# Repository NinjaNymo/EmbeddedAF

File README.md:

# EmbeddedAF
This repository contains the source code and hardware design files for a indoor automated urban farming system. 

The system has a master/slave architecture, where the master is refered to as the _master_, while the slaves as the _nodes_.

### **_The Concept:_**
The idea was to use a wireless sensor network system as a case study in an embedded systems development process.

Due to the master/slave architecture of the system, the project covers both embedded C development on the node devices and embedded Linux development on the master device, as well as communication over ZigBee between the two.

All in all; a good variation of challanges to learn more about embedded systems.

### **_The Node:_**

The node features a 16-bit MCU and a XBee 3 ZigBee module on an in-house developed and etched PCB. An OLED display and buttons are included on the board such that the node device can be used in an _offline mode_ independetly of the master device.

The node device measures temperature on the PCB and interfaces with 1) external digital temperature sensors, 2) an external analog soil moisture sensor and 3) an external relay that controls a grow-light.

The idea is to control the grow-light on a day/night-like cycle and record and publish the temperature and soil moisture measurements to the master device.

* The firmware is written in C, and can be found in [/src/node/](/src/node).
* The schematic and PCB is designed in Eagle, and can be found in [/Eagle/node/](/Eagle/node/).

This repository contains stuff for a project on embedded automatic farming.

That includes circuit schematics, PCB designs and code to run on the two systems:

1. **The node:** A board with a 16-bit MCU and a XBee 3 micro module. It features two temperature sensors and one analog soil moisture sensor as well as I/O for offline availiability. The source found in src/node is written C and compiles with XC16.
2. **The master:** A Raspberry Pi 2B mounted with the same XB3 modules as the nodes. It runs Raspbian Stretch lite, a MQTT broker, a Node.js server that provides a web ui and finally a MQTT-SN gateway that is implemented in python and who's source code is found in src/master.

In addition there are some random python scripts, diagrams in the DrawIO folder, prototype schematics and board designs.

### The concept:

The idea here is to use a wireless sensor network system inteded to be used in indoor automatic farming as a case study in a development process.

I like watching things grow, and I think indoor has interesting benefits over traditional outdoor farming such as reduced water consumption, seasonal independence and a shorter logistic travel distance so perhaps some day all this might turn into something.

To do automated farming, it controls a LED lamp on a day/night-like cycle which can be configured through the on-board user interface or wirelessly.

The lamp and power distribution needs some work and will be put up here once it is up to spec. 

Further the node measures water content in soil which is intended to be used with automated watering. It has a Dallas 1-wire bus on one of it connectors which currently run both an on-board temp sensor and an external waterproof one that I planned on sticking in the soil.

The MCU does everything mentioned above, and UARTs with the XB3 which handle MQTT over ZigBee.

With many of these and an online master device from which you can monitor and control the whole setup it should be possible to realize indoor automated farming.

### Technical details:

#### The node:
* Microchip PIC24FJ128GA202 MCU. 16-bit.
* Digi XB3-24Z8UM RF module running ZigBee 3.0 API as a router.
* Maxim DS18B20 temperature sensors.
* Analog capacative soil moisture sensor.
* SSD1306 OLED display driver.
*

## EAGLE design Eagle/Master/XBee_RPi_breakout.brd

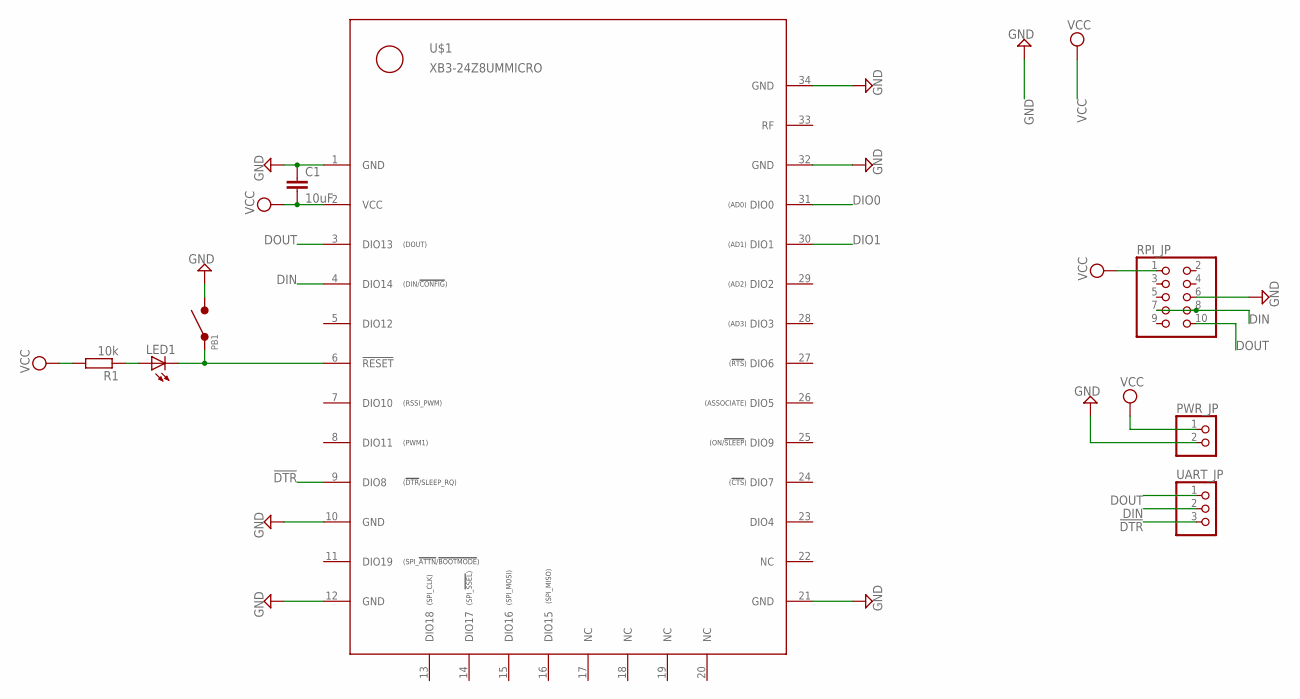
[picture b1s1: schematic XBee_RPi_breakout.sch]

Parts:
C1: 10uF; C0805
LED1: LEDSML0805; SML0805
PB1: PUSHBUTTON_2LEG; PUSHBUTTON_6X3.5MM
PWR_JP: PINHD-1X2; 1X02
R1: 10k; M0805
RPI_JP: PINHD-2X5; 2X05
U$1: XB3-24Z8UMMICRO; XBEE3_MICRO
UART_JP: PINHD-1X3; 1X03

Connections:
!DTR: U$1.9 (DIO8), UART_JP.3
!RST: LED1.C, PB1.P$1, U$1.6 (!RESET)
DIN: RPI_JP.7, RPI_JP.8, U$1.4 (DIO14), UART_JP.2
DIO0: U$1.31 (DIO0)
DIO1: U$1.30 (DIO1)
DOUT: RPI_JP.10, U$1.3 (DIO13), UART_JP.1
GND: C1.1, PB1.P$2, PWR_JP.2, RPI_JP.6, U$1.1 (GND), U$1.10 (GND), U$1.12 (GND), U$1.21 (GND), U$1.32 (GND), U$1.34 (GND)
unnamed: LED1.A, R1.1
VCC: C1.2, PWR_JP.1, R1.2, RPI_JP.1, U$1.2 (VCC)

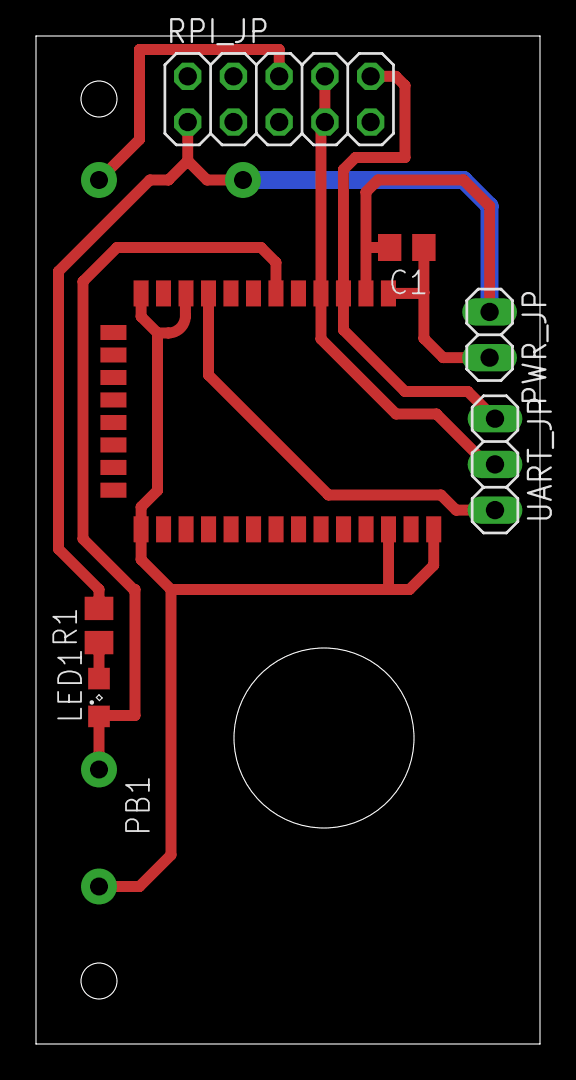
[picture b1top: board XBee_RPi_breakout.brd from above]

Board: 2 copper layers, 28.0 x 56.0 mm, 8 parts (0 on the bottom side), 7 nets.

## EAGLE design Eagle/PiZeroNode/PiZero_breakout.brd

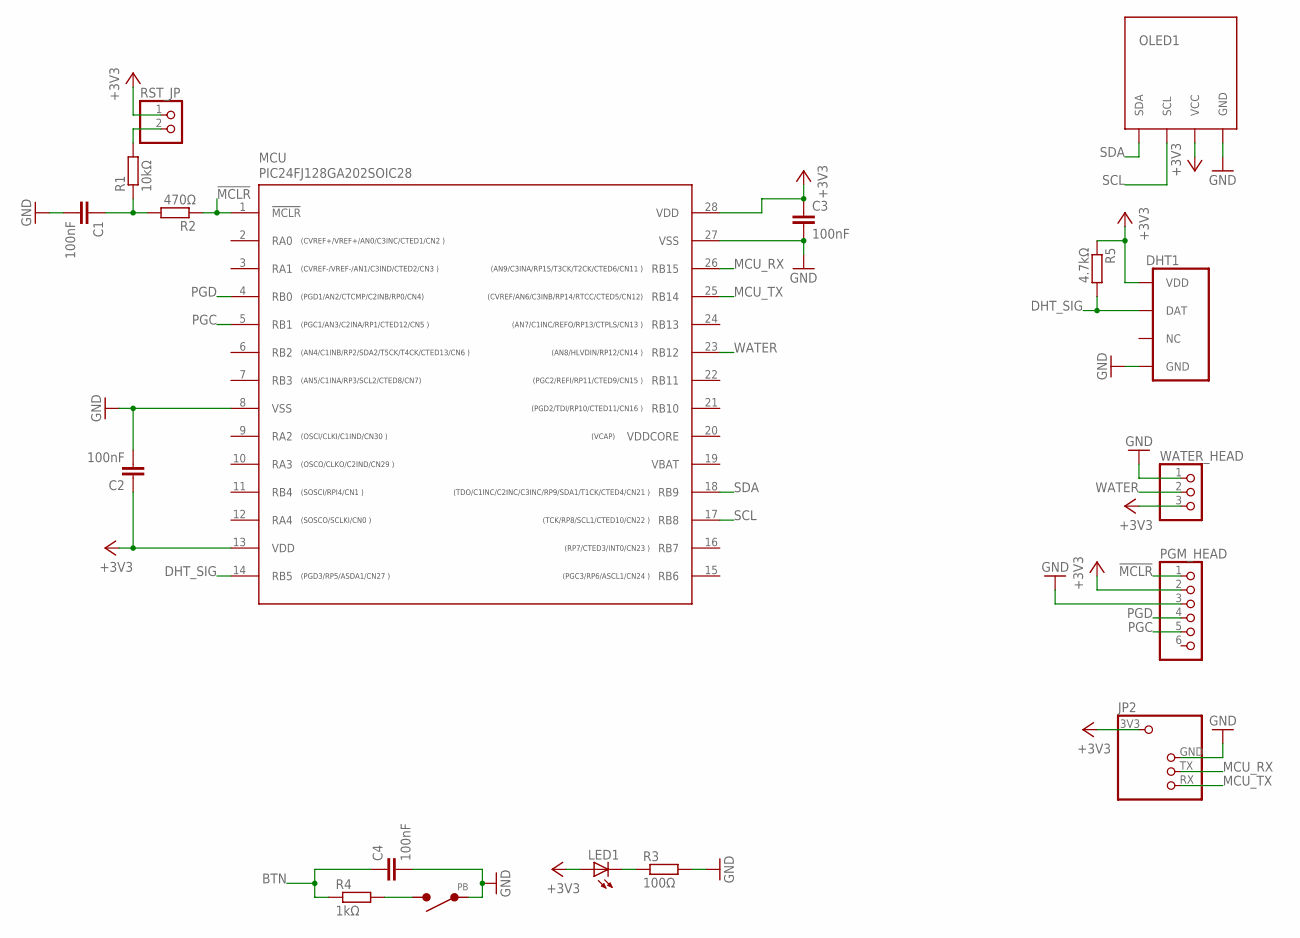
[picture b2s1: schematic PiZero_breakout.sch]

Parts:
C1, C2, C3, C4: 100nF; C0805
DHT1: DHT11VERT; DHT11
JP2: RPI_UART_HEADER; RPI_UART_HEAD
LED1: LEDCHIPLED_0805; CHIPLED_0805
MCU: PIC24FJ128GA202SOIC28; SOIC28L
OLED1: OLED_4PIN_I2C; OLED_4PIN
PB: PUSHBUTTON_2LEG; PUSHBUTTON_6X3.5MM
PGM_HEAD: PINHD-1X6; 1X06
R1: 10kΩ; R0805
R2: 470Ω; R0805
R3: 100Ω; R0805
R4: 1kΩ; R0805
R5: 4.7kΩ; R0805
RST_JP: PINHD-1X2; 1X02
WATER_HEAD: PINHD-1X3; 1X03

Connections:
!MCLR: MCU.1 (!MCLR), PGM_HEAD.1, R2.1
+3V3: C2.1, C3.1, DHT1.VDD, JP2.3V3, LED1.A, MCU.13 (VDD), MCU.28 (VDD), OLED1.VCC, PGM_HEAD.2, R5.1, RST_JP.1, WATER_HEAD.3
BTN: C4.1, R4.1
DHT_SIG: DHT1.DAT, MCU.14 (RB5), R5.2
GND: C1.2, C2.2, C3.2, C4.2, DHT1.GND, JP2.GND, MCU.8 (VSS), MCU.27 (VSS), OLED1.GND, PB.P$1, PGM_HEAD.3, R3.2, WATER_HEAD.1
MCU_RX: JP2.TX, MCU.26 (RB15)
MCU_TX: JP2.RX, MCU.25 (RB14)
unnamed: C1.1, R1.1, R2.2
unnamed: LED1.C, R3.1
unnamed: R1.2, RST_JP.2
unnamed: PB.P$2, R4.2
PGC: MCU.5 (RB1), PGM_HEAD.5
PGD: MCU.4 (RB0), PGM_HEAD.4
SCL: MCU.17 (RB8), OLED1.SCL
SDA: MCU.18 (RB9), OLED1.SDA
VDDCORE: MCU.20 (VDDCORE)
WATER: MCU.23 (RB12), WATER_HEAD.2

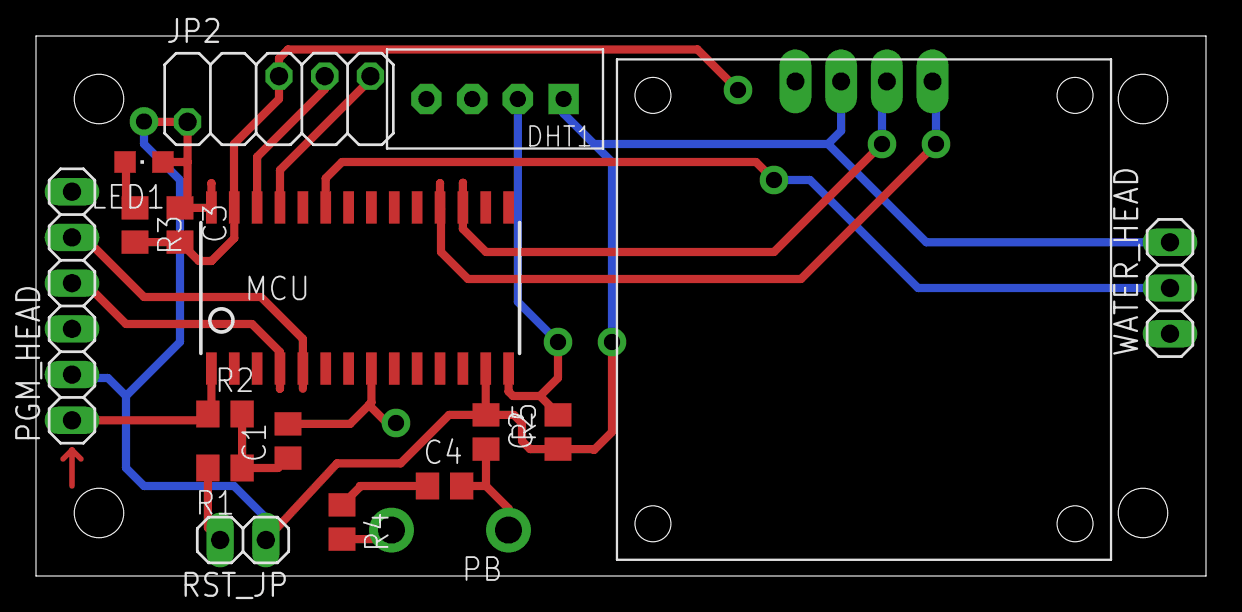
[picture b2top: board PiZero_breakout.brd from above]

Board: 2 copper layers, 65.0 x 30.0 mm, 18 parts (0 on the bottom side), 16 nets.

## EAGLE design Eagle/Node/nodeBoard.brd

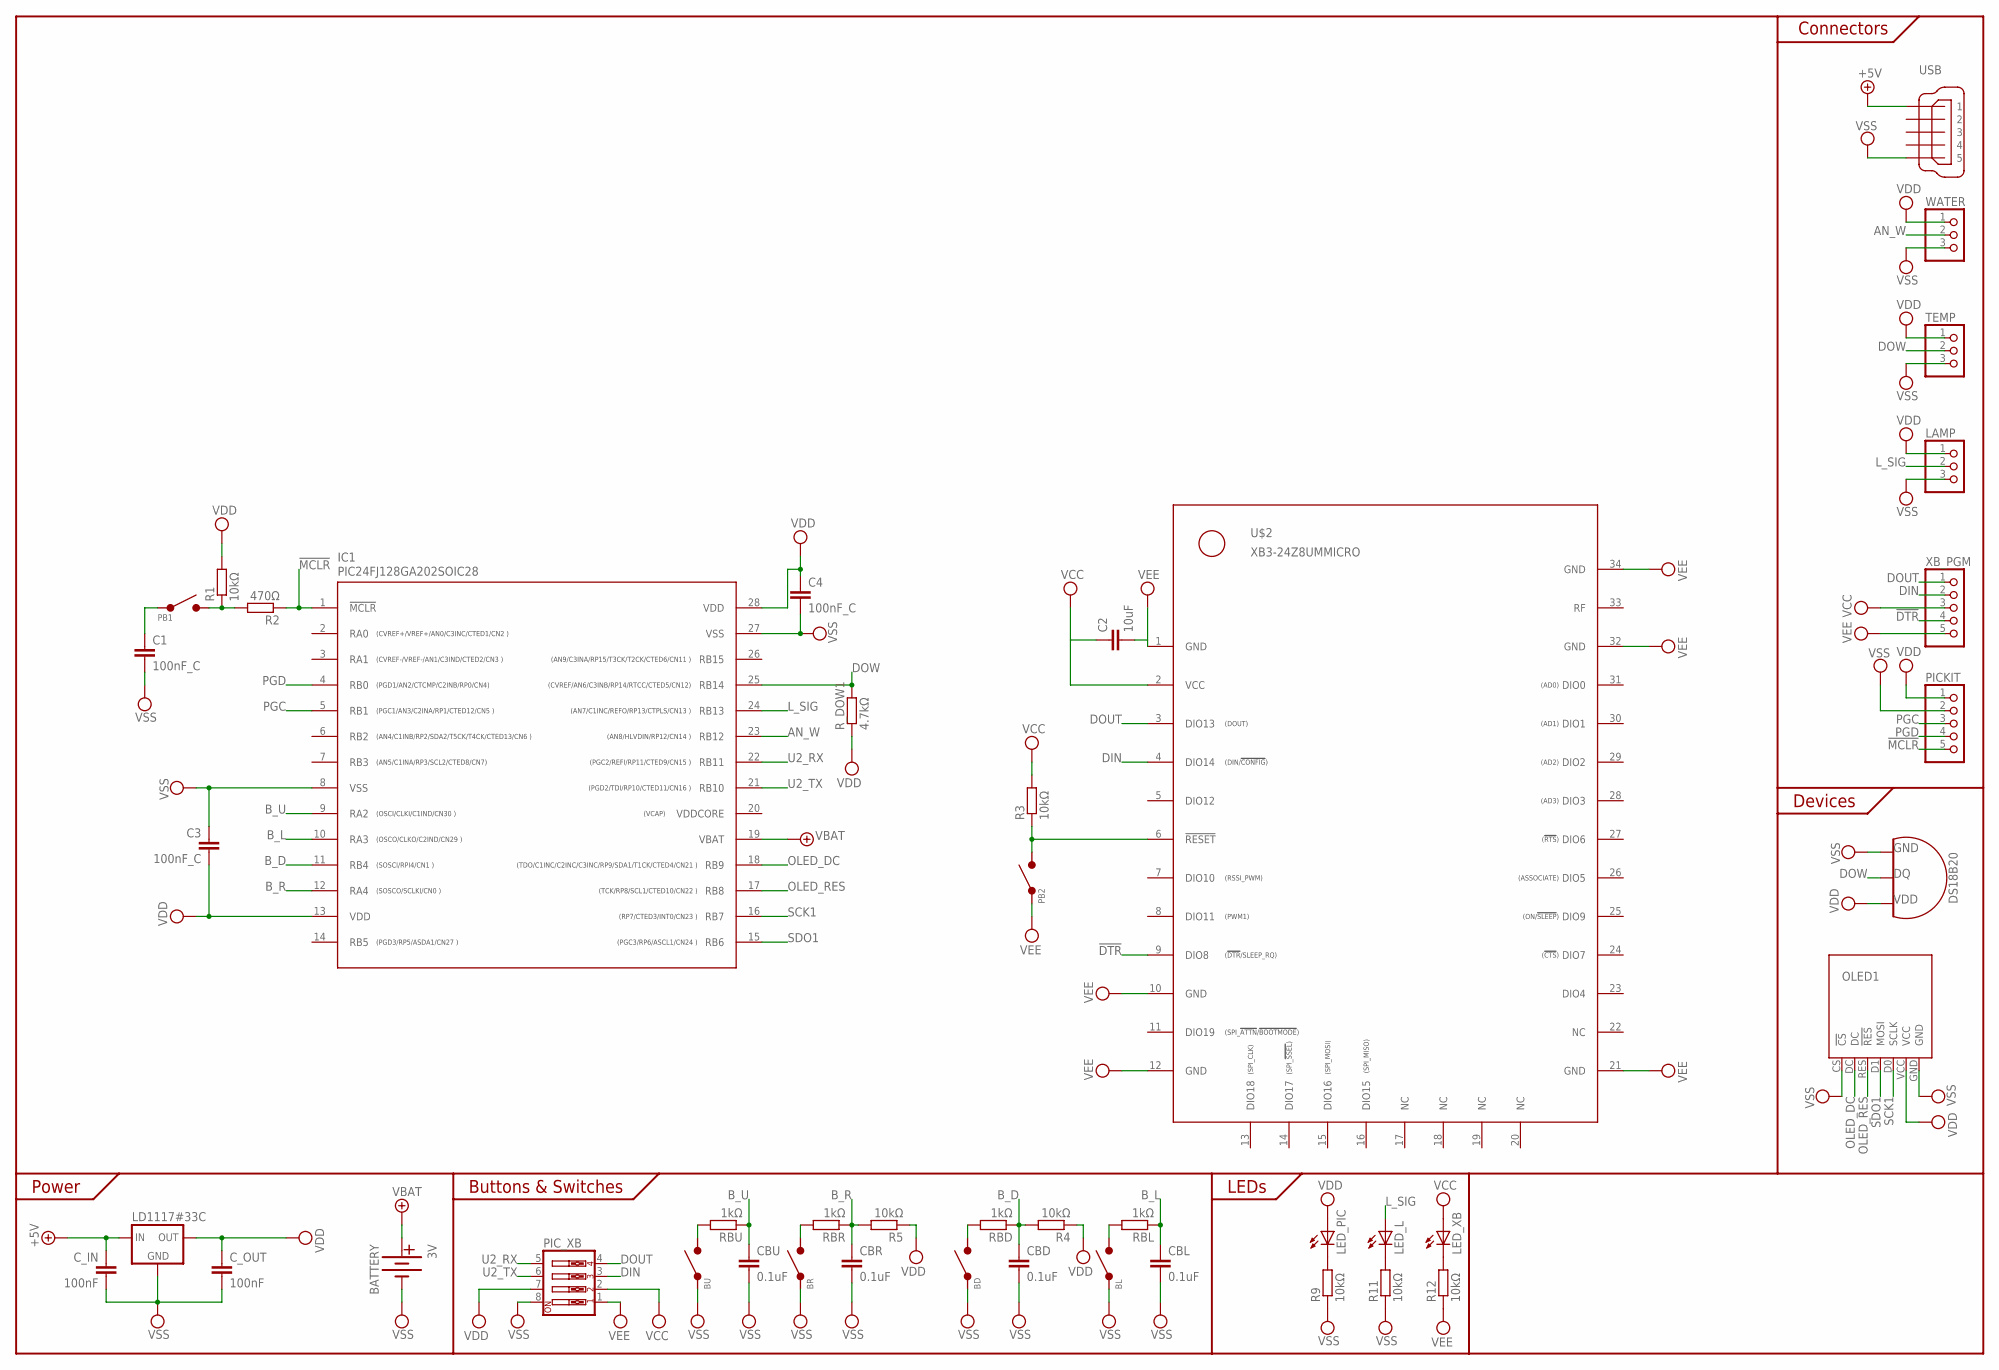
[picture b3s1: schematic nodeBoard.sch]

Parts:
3V: BATTERY; 20MM_CELLHOLDER
BD: PUSHBUTTON_4LEG_SMD; TACTILE_SWITCH_SMD_6.2MM_BROWN
BL: PUSHBUTTON_4LEG_SMD; TACTILE_SWITCH_SMD_6.2MM_BROWN
BR: PUSHBUTTON_4LEG_SMD; TACTILE_SWITCH_SMD_6.2MM_BROWN
BU: PUSHBUTTON_4LEG_SMD; TACTILE_SWITCH_SMD_6.2MM_BROWN
C1, C3, C4: 100nF_C; C0805
C2: 10uF; C0805
CBD: 0.1uF; C0805
CBL: 0.1uF; C0805
CBR: 0.1uF; C0805
CBU: 0.1uF; C0805
C_IN: 100nF; C0805
C_OUT: 100nF; C0805
IC1: PIC24FJ128GA202SOIC28; SOIC28L
LAMP: PINHD-1X3; 1X03
LED_L: LEDCHIPLED_0805; CHIPLED_0805
LED_PIC: LEDCHIPLED_0805; CHIPLED_0805
LED_XB: LEDCHIPLED_0805; CHIPLED_0805
OLED1: OLED_7PIN_SPI; OLED_7PIN
PB1, PB2: PUSHBUTTON_2LEG; PUSHBUTTON_6X3.5MM
PICKIT: PINHD-1X5; 1X05
PIC_XB: SW_DIP-4; EDG-04
R1, R3, R4, R5, R9, R11, R12: 10kΩ; R0805
R2: 470Ω; R0805
RBD: 1kΩ; R0805
RBL: 1kΩ; R0805
RBR: 1kΩ; R0805
RBU: 1kΩ; R0805
R_DOW1: 4.7kΩ; R0805
TEMP: PINHD-1X3; 1X03
U$1: LD1117#33C; DPACK
U$2: XB3-24Z8UMMICRO; XBEE3_MICRO
U$7: DS18B20; TO92
USB: MINI-USB-32005-201; 32005-201
WATER: PINHD-1X3; 1X03
XB_PGM: PINHD-1X5; 1X05

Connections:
!DTR: U$2.9 (DIO8), XB_PGM.4
!MCLR: IC1.1 (!MCLR), PICKIT.5, R2.1
+5V: C_IN.1, U$1.3 (IN), USB.1
AN_W: IC1.23 (RB12), WATER.2
B_D: CBD.1, IC1.11 (RB4), R4.2, RBD.1
B_L: CBL.1, IC1.10 (RA3), RBL.1
B_R: CBR.1, IC1.12 (RA4), R5.2, RBR.1
B_U: CBU.1, IC1.9 (RA2), RBU.1
DIN: PIC_XB.3, U$2.4 (DIO14), XB_PGM.2
DOUT: PIC_XB.4, U$2.3 (DIO13), XB_PGM.1
DOW: IC1.25 (RB14), R_DOW1.2, TEMP.2, U$7.2 (DQ)
L_SIG: IC1.24 (RB13), LAMP.2, LED_L.A
unnamed: C1.1, PB1.P$1
unnamed: PB2.P$2, R3.1, U$2.6 (!RESET)
unnamed: PB1.P$2, R1.1, R2.2
unnamed: BU.B1, BU.B2, RBU.2
unnamed: BL.B1, BL.B2, RBL.2
unnamed: BR.B1, BR.B2, RBR.2
unnamed: BD.B1, BD.B2, RBD.2
unnamed: LED_L.C, R11.2
unnamed: LED_XB.C, R12.2
unnamed: LED_PIC.C, R9.2
OLED_DC: IC1.18 (RB9), OLED1.DC
OLED_RES: IC1.17 (RB8), OLED1.RES (!RES)
PGC: IC1.5 (RB1), PICKIT.3
PGD: IC1.4 (RB0), PICKIT.4
SCK1: IC1.16 (RB7), OLED1.D0 (SCLK)
SDO1: IC1.15 (RB6), OLED1.D1 (MOSI)
U2_RX: IC1.22 (RB11), PIC_XB.5
U2_TX: IC1.21 (RB10), PIC_XB.6
VBAT: 3V.+@1 (+), 3V.+@2 (+), IC1.19 (VBAT)
VCC: C2.1, LED_XB.A, PIC_XB.2, R3.2, U$2.2 (VCC), XB_PGM.3
VDD: C3.2, C4.1, C_OUT.1, IC1.13 (VDD), IC1.28 (VDD), LAMP.1, LED_PIC.A, OLED1.VCC, PICKIT.1, PIC_XB.7, R1.2, R4.1, R5.1, R_DOW1.1, TEMP.1, U$1.2 (OUT), U$7.3 (VDD), WATER.1
VDDCORE: IC1.20 (VDDCORE)
VEE: C2.2, PB2.P$1, PIC_XB.1, R12.1, U$2.1 (GND), U$2.10 (GND), U$2.12 (GND), U$2.21 (GND), U$2.32 (GND), U$2.34 (GND), XB_PGM.5
VSS: 3V.-, BD.A1, BD.A2, BL.A1, BL.A2, BR.A1, BR.A2, BU.A1, BU.A2, C1.2, C3.1, C4.2, CBD.2, CBL.2, CBR.2, CBU.2, C_IN.2, C_OUT.2, IC1.8 (VSS), IC1.27 (VSS), LAMP.3, OLED1.CS (!CS), OLED1.GND, PICKIT.2, PIC_XB.8, R9.1, R11.1, TEMP.3, U$1.1 (GND), U$7.1 (GND), USB.5, WATER.3

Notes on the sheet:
Power
Connectors
Buttons & Switches
Devices
LEDs

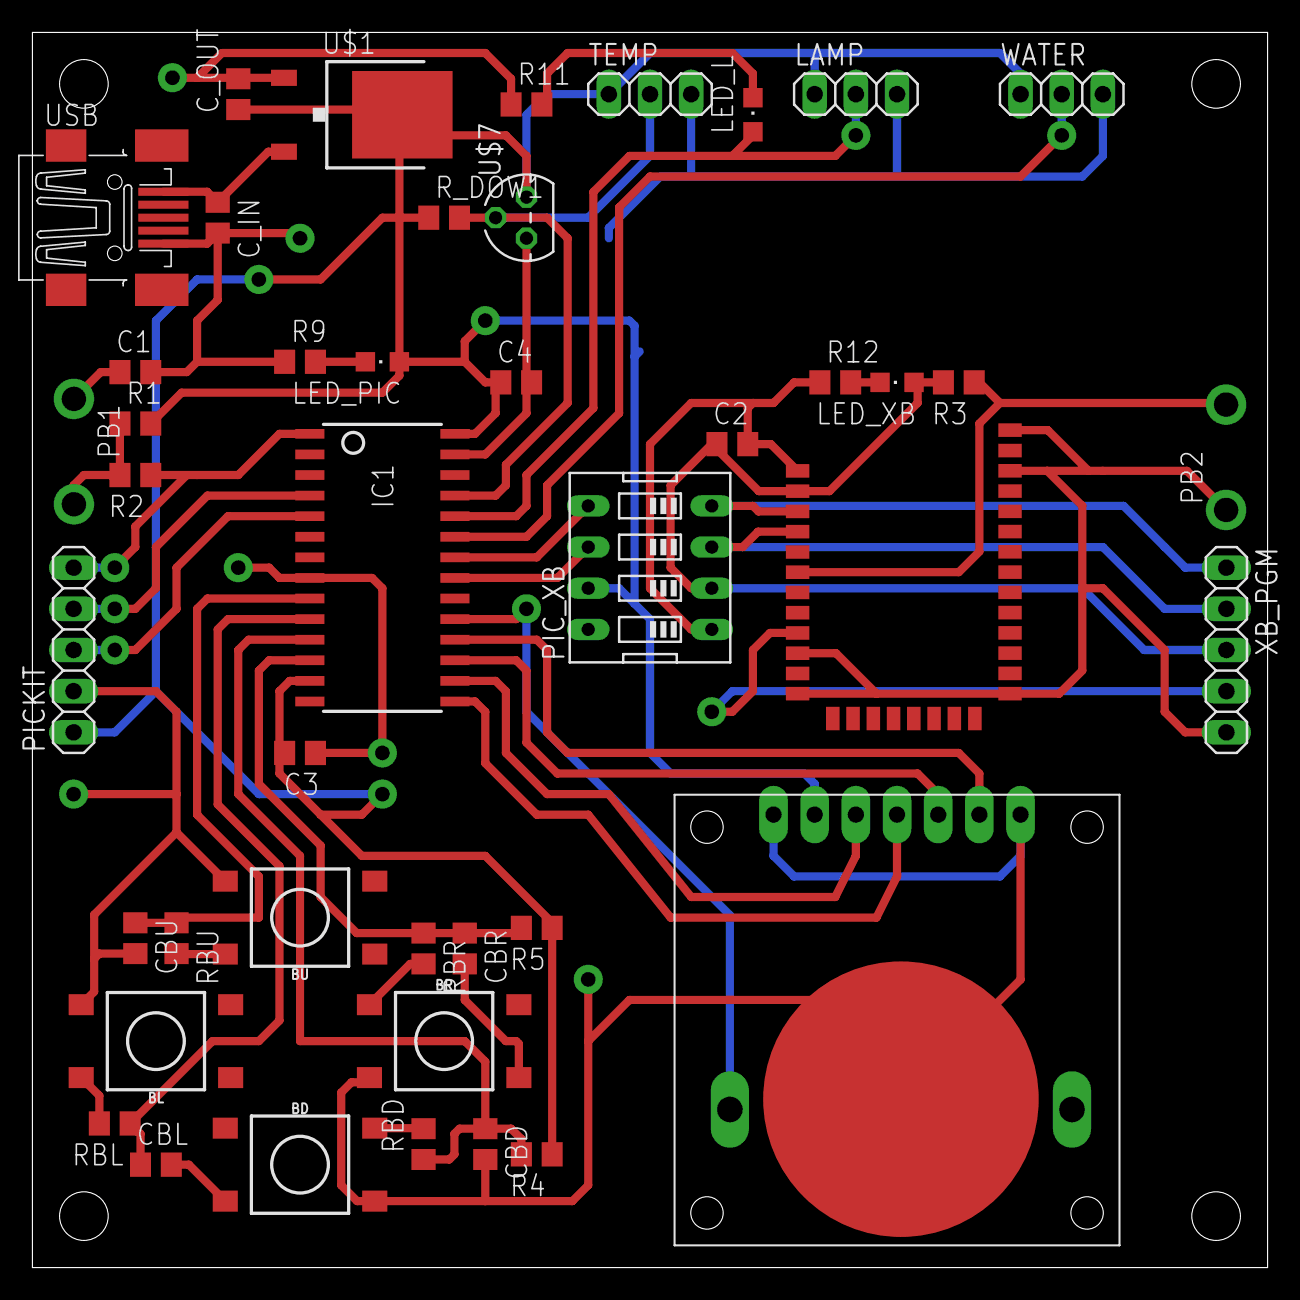
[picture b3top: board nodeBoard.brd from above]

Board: 2 copper layers, 76.2 x 76.2 mm, 45 parts (0 on the bottom side), 35 nets.

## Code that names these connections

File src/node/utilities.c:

//   _____ _____ _____
//  |   | |__   |   | | EmbeddedAF/src/node/utilities.c
//  | | | |   __| | | | Nikolai Nymo
//  |_|___|_____|_|___| 06-02-18

#include <xc.h>
#include <stdio.h>
#include "utilities.h"

uint16_t maxADC = 2740;
uint16_t minADC = 2250;

void util_initPins(){
    // Disable ADCs:
    ANSA = 0x0000;
    ANSB = 0x0000;
    
    // Pushbuttons:
    //
    // Data direction:
    TRISAbits.TRISA2  = 1; // RA2 = input
    TRISAbits.TRISA3  = 1; // RA3 = input
    TRISAbits.TRISA4  = 1; // RA4 = input
    TRISBbits.TRISB4  = 1; // RB3 = input
    // Pull-ups:
    CNPU2bits.CN30PUE = 1; // Pull-up enable on RA2/CN30
    CNPU2bits.CN29PUE = 1; // Pull-up enable on RA3/CN29
    CNPU1bits.CN0PUE  = 1; // Pull-up enable on RA4/CN0
    CNPU1bits.CN1PUE  = 1; // Pull-up enable on RB4/CN1
    // Input change interrupt:
    CNEN1bits.CN0IE   = 1; // RA4/CN0 triggers CN interrupt
    CNEN1bits.CN1IE   = 1; // RB4/CN1 triggers CN interrupt
    CNEN2bits.CN29IE  = 1; // RA3/CN29 triggers CN interrupt
    CNEN2bits.CN30IE  = 1; // RA2/CN30 triggers CN interrupt
    
    // Lamp control:
    //
    TRISBbits.TRISB13 = 0; // RB13 = output
    
    // Peripheral pin select (PPS):
    //
    __builtin_write_OSCCONL(OSCCON & 0xDF); // to clear IOLOCK
    // Outputs:
    RPOR3bits.RP6R    =  7; // SPI1 DO    --> Pin RB6/RP6
    RPOR3bits.RP7R    =  8; // SPI1 CLK   --> Pin RB7/RP7
    RPOR5bits.RP10R   =  3; // UART 1 TX  --> Pin RB10/RP10
    // Inputs:
    RPINR18bits.U1RXR = 11; // UART 1 RX  --> Pin RB11/RP11
    __builtin_write_OSCCONL(OSCCON | 0x40); // to set IOLOCK  
}

void util_initADC(){
    // NOTE: All ADC register are 0x0000 as default.
    
    // Pin configuration:
    //
    TRISBbits.TRISB12  = 1; // RB12 = input
    ANSBbits.ANSB12    = 1; // RB12 = analog
    
    // ADC configuration:
    //
    AD1CON1bits.MODE12 =          1; // 12-bit A/D operation
    AD1CON1bits.SSRC   =     0b0111; // Auto convert after sampling is done
    AD1CON1bits.FORM   =       0b00; // Output = absolute decimal, unsigned
    AD1CON3bits.ADCS   = 0b00000011; // T_AD = 6 * T_CY
    AD1CON3bits.SAMC   =    0b11111; // Sample time =  31 * T_AD
    AD1CHSbits.CH0SA   =    0b01000; // Sample AN8 on pin RB12
    
    AD1CON1bits.ADON   =          1; // Enable module
}

static uint16_t util_readADC(){
    AD1CON1bits.SAMP = 1;     // Start sampling
    while(!AD1CON1bits.DONE); // Wait until conversion is done
    AD1CON1bits.SAMP = 0;     // Stop sampling
    return ADC1BUF0;          // Return value
}

uint8_t util_getWaterLevel(){
    uint8_t val = ((util_readADC() - minADC) * 100) / (maxADC - minADC);
    if (val > 100){
        val = 100;
    }
    return 100 - val;
}

void util_runLampFSM(systemState_t* state){
    if(state->sunrise == state->sunset){
        state->lampState = OFF;
        return;
    }
    
    // Cus it makes it way more readable:
    uint8_t sr = state->sunrise;
    uint8_t SS = state->sunset;
    uint8_t HH = state->time.hour;
    
    // if(((SS <= HH) && (HH < sr)) || ((sr < HH) && SS <= HH) ){

    switch(state->lampState){
        case ON:
            PORTBbits.RB13 = 1;
            if((SS <= HH) || (HH < sr)){
                PORTBbits.RB13 = 0;
                state->lampState = OFF;
            }    
            break;
        case OFF:
            PORTBbits.RB13 = 0;
            if((sr <= HH) && (HH < SS)){
                PORTBbits.RB13 = 1;
                state->lampState = ON;
            }
            else if(SS < sr){
                if(((HH < SS) && (HH < sr)) || ((SS < HH) && (sr < HH))){
                    PORTBbits.RB13 = 1;
                    state->lampState = ON;
                }
            }
            break;
        case SUS_ON:
            PORTBbits.RB13 = 1;
            break;
        case SUS_OFF:
            PORTBbits.RB13 = 0;
            break;
        default:
            break;
    }
}

void util_initInterrupts(){
    INTCON1bits.NSTDIS = 1; // Disable nested interrupts
    
    // UART 1 RX:
    IFS0bits.U1RXIF = 0; // Clear UART 1 RX interrupt flag
    IEC0bits.U1RXIE = 1; // Enable UART 1 RX interrupt
    
    // Timer 2/3:
    IFS0bits.T3IF   = 0; // Clear Timer 3 interrupt flag
    IEC0bits.T3IE   = 1; // Enable Timer 3 interrupt
    
    // RTC alarm:
    IFS3bits.RTCIF  = 0; // Clear RTC interrupt flag
    IEC3bits.RTCIE  = 1; // Enable RTC 
    
    // Input change (CN):
    IFS1bits.CNIF   = 0; // Clear CN interrupt flag
    IEC1bits.CNIE   = 1; // Enable CN interrupt
}

void util_initTimer23(){
    T2CONbits.T32   =    1; // Set timer to 32-bit
    T2CONbits.TCKPS = 0b11; // 256 clock pre scale
    
    // For 10 seconds, trigger interrupt at 156250 = 0x0002625A
    // For 30 seconds, trigger interrupt at 468750 = 0x0007270E
    // For 60 seconds, trigger interrupt at 937500 = 0x000E4E1C

    PR3 = 0x0007; // Most significant word of compare value
    PR2 = 0x270E; // Least significant word of compare value
}

void util_startTimer23(){
    T2CONbits.TON = 1;
}

void util_stopTimer23(){
    T2CONbits.TON = 0;
    // Reset timer
    TMR2 = 0;
    TMR3 = 0;
}

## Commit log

2018-05-15 Add gitignore from old project
2018-05-15 Add files from old project
2018-05-15 Change from periodic timer to RTC alarm
2018-05-21 Add Change Node ID menu
2018-05-21 Add UseCase diagram
2018-05-21 Add CONNACK frame
2018-05-21 Make UART continue in IDLE mode
2018-05-21 Add small delay when sending frames for stability
2018-05-21 Add refresh time as RTC_INIT parameter
2018-05-21 Add more MQTT macros
2018-05-21 Add functions for publishing sensor values
2018-05-21 Made variables changed by ISRs volatile
2018-05-21 Add start and stop functions for Timer 2/3
2018-06-01 Add master diagrams
2018-06-01 Add completed master code from local repo
2018-06-01 Node code tested and working
2018-06-01 Add node hardware structure diagram
2018-06-13 Add some diagrams
2018-06-13 Add PowerBoard eagle project
2018-07-16 Backup changes
2018-12-24 Create Docs folder
2018-12-24 Add png
2018-12-24 Add photos
2018-12-24 Add pictures to readme
2018-12-24 Updates to main/readme
